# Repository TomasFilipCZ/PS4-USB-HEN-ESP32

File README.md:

<h1 align="center">PS4 USB Flash Emulator with ESP32-S2 (PS4-USB-ESP32)</h1>

<p>Small electronic board to support automatic loading HEN in PS4 with ESP32. Project using method discovered on PS4 Firmware 9.00, where user need manually plug USB flash drive in right time to load HEN. 

Together with  ESP32-S2 as WebServer will PS4-USB-ESP32 emulate USB Flash drive, causing automatic loading HEN in desired time without user interaction.

Project is modification of "PS4 Server 9.00" and "ESP8266 Control device", aim is to share design data of small PCB and firmware for the ESP32-S2 to create device for wide  usage of automatic loading and implement basic electronic protection for PS4.

Differents to standard market ESP32-S2 eval kits are:
- ESP32-S2 plan to use is in version with 16MBytes (but can be use ESP32-S2 with 4Mbytes)
- MicroSD card in 4bit mode (can be configured to SPI mode)
- Direct USB OTG connection to emulate Flash Drive
- ESD protections and RGB LED 
 </p>

<i>Status</i>
<b> 06.03.2022 - you can buy first protypes on  [ebay](https://www.ebay.de/itm/165370662367)</b>

## Project requirements
- Micro SD card (prefered 4Gbyte, standard SDHC formated as FAT32)
- USB 2.0 data cable ( is recommend to not exceed length of 1.8M )
- Binary loader for the ESP32-S2

## Links
PS4-USB-HEN32 needs firmware to run WebServer with DHCP/DNS service, you can programm device either by 
 - [Karo](https://karo218.ir/espweb/ "Karo ESP programming method") or 
 - [XHOST-PRO ](https://t.co/l7LI6YW8ns "XHOST-Pro programming method") 

To program board, you need 
1. Hhold Reset Button,
2. Press Boot button and 
3. release Reset Button and release Boot button

(Serial ports and USB-ESP-S2 device is appear in the system)

## Setup
- Plug PS4-USB-HEN32 with micro USB cable to PS4. Due Webserver/DNS capability  web page with HEN  can be access through 'User Guide/Helpful Info' in PS4  <i>(required successful Wifi connection to PS4-USB-HEN32, password '12345678'</i> )

## Pictures

3D Picture of PCBA 

## Project structure

- PCB Design data are developed in KiCad 5.1.10
- directory <b>bom</b> contains JLCPCB compatible BOM,after product check later full BOM 
- directory <b>gerber</b> contains gerbers files with pick-up place file. Components are located only in TOP layer. 
- directory <b>libs </b> contains project specific  library

note:   PS4-USB-ESP32 project used module ESP32-S2, severals version may be supported
 - <b>ESP32-S2-WROVER(16MB) - preferred </b>
 - ESP32-S2-WROOM or ESP32-S2-WROVER (4MB)

## Future Updates

- [X] Figure out, if 4-bit SD card mode is working, check the design (but not EMMC_SD library, not supported by ESP32-S2)
- [X] Create STEP/STL Model of Plastic BOX to be able printed in 3D Printer
- [X]  Waiting for Delivering PCB to test all complete designs

##Update in 1.1 Version
- Use transistor level shifter for RGB LED. RGB led is now powered from 5V to be brighter. 
- PCB will goes to black and thickness to 1.0mm therefore CAD design needs to be fine tune 

## Author

**Tomas Filip**

- [Profile](https://github.com/TomasFilipCZ "Tomas Filip on GitHub")
- [Join us on Discord](https://discord.gg/DWephJvzwR "Discord Server")

## 🤝 Support

Contributions, issues, and feature requests are welcome!

if you like this project, stay tuned !

<i>Special thanks: Karo, ChendoChap, stooged, xps3riments for their work and thanks to all community helper and developer on PS scene.  It's really fun...</i>

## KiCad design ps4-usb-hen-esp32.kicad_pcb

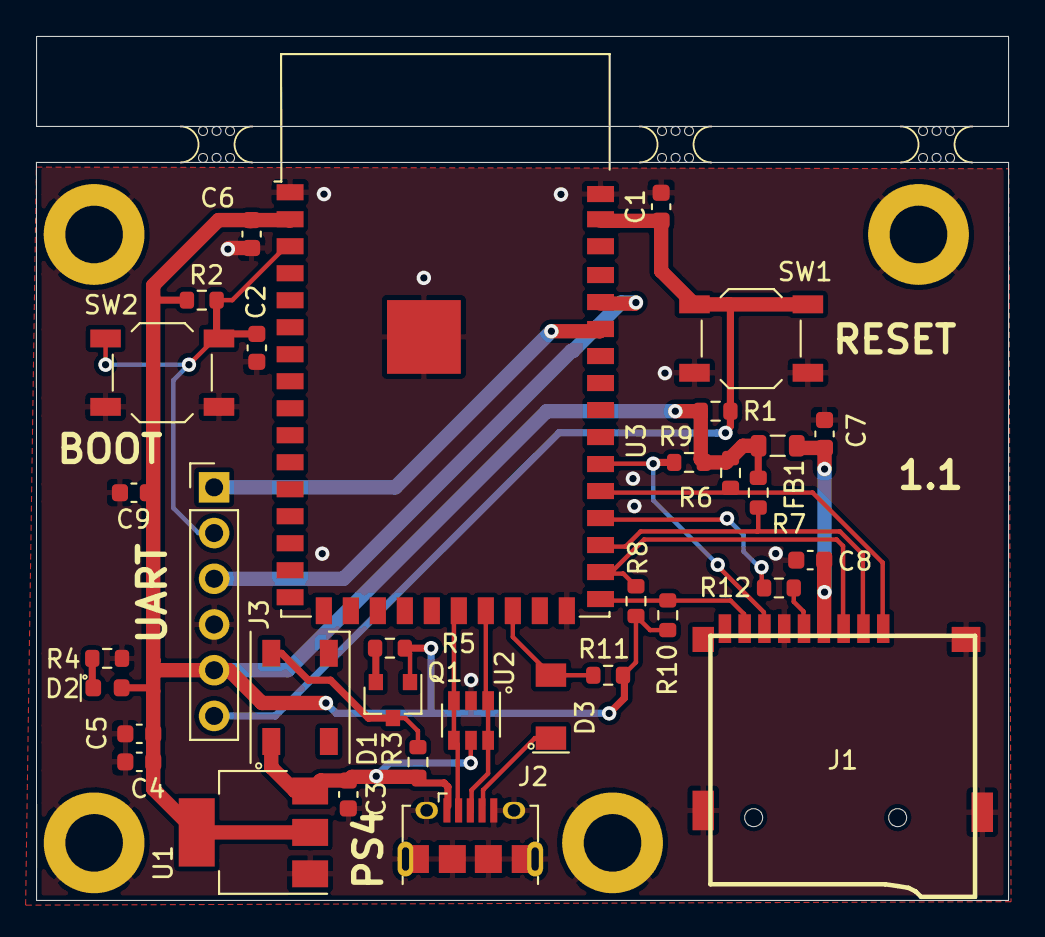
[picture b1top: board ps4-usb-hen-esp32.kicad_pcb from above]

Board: 2 copper layers, 54.0 x 48.0 mm, 41 parts (0 on the bottom side), 22 nets.

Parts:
C1, C2, C3, C4, C6, C8, C9: 100nF; C_0603_1608Metric
C5, C7: 10uF_10V; C_0603_1608Metric
D1: WS2812B; LED_WS2812B_PLCC4_5.0x5.0mm_P3.2mm
D2: D_LED_0603_Red; LED_0603_1608Metric
D3: LL4148; D_MiniMELF
FB1: 100MHz/600Ohm/500mA; L_0805_2012Metric
H1, H2, H3, H4: MountingHole_Pad_M3; MountingHole_3.2mm_M3_DIN965_Pad
J1: Micro_SD_Card_Det; GCT-MEM2055-00-190-01-A
J2: USB_B_Micro; USB_Micro-Jing Extension
J3: Conn_01x06; PinHeader_1x06_P2.54mm_Vertical
Q1: 2N7002; SOT-23
R1, R2, R3, R5, R6, R7, R8, R9, R10, R11: 10k; R_0603_1608Metric
R4: 330R; R_0603_1608Metric
R12: 22R; R_0603_1608Metric
SW1, SW2: SW_Push; SW_SPST_TL3342
U1: AMS1117-3.3; SOT-223-3_TabPin2
U2: SRV05-4; SOT-23-6
U3: ESP32-S2-WROVER-16MB; ESP32-S2-WROVER
mouse-bite-2mm-slot, mouse-bite-2mm-slot#2, mouse-bite-2mm-slot#3: VAL**; mouse-bite-2mm-slot

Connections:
+3V3: C4.1, C5.1, C6.2, C9.2, D2.2, FB1.2, J3.5, Q1.1, R1.1, R2.1, R5.1, R6.2, R7.2, R8.2, R9.2, R10.2, R11.1, U1.2, U3.2
+5V: C3.1, D1.1, J2.1, R3.1, U1.3, U2.5
/BUT: C2.1, J3.2, R2.2, SW2.1, U3.3
/ESP_EN: C1.1, J3.6, R1.2, SW1.1, U3.41
/GPIO18_5V: D1.4, Q1.3, R3.2
/RXD: J3.3, U3.38
/SD_CLK: R12.2, U3.30
/SD_CLK_R: J1.5, R12.1
/SD_CMD: J1.3, R8.1, U3.28
/SD_DAT0: J1.7, R9.1, U3.32
/SD_DAT1: J1.8, R10.1, U3.27
/SD_DAT2: J1.1, R6.1, U3.31
/SD_DAT3: J1.2, R7.1, U3.29
/TXD: J3.1, U3.37
/USB_D+: J2.3, U2.1, U2.6, U3.23
/USB_D-: J2.2, U2.3, U2.4, U3.22
/USB_ID: D3.2, R11.2, U3.24
/USB_ID_C: D3.1, J2.4
GND: C1.2, C2.2, C3.2, C4.2, C5.2, C6.1, C7.2, C8.2, C9.1, D1.3, H1.1, H2.1, H3.1, H4.1, J1.6, J1.11, J2.5, J2.6, J3.4, R4.1, SW1.2, SW2.2, U1.1, U2.2, U3.1, U3.26, U3.42, U3.43
unnamed: D2.1, R4.2
unnamed: Q1.2, R5.2
Vdrive: C7.1, C8.1, FB1.1, J1.4

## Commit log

2022-01-31 first issue
2022-01-31 fix marking/text, and few adjustment
2022-03-06 change RGB LED to 5V, add level shifter, change thickness of PCB to 1.0mm, add simple box with FreeCad, update readme
